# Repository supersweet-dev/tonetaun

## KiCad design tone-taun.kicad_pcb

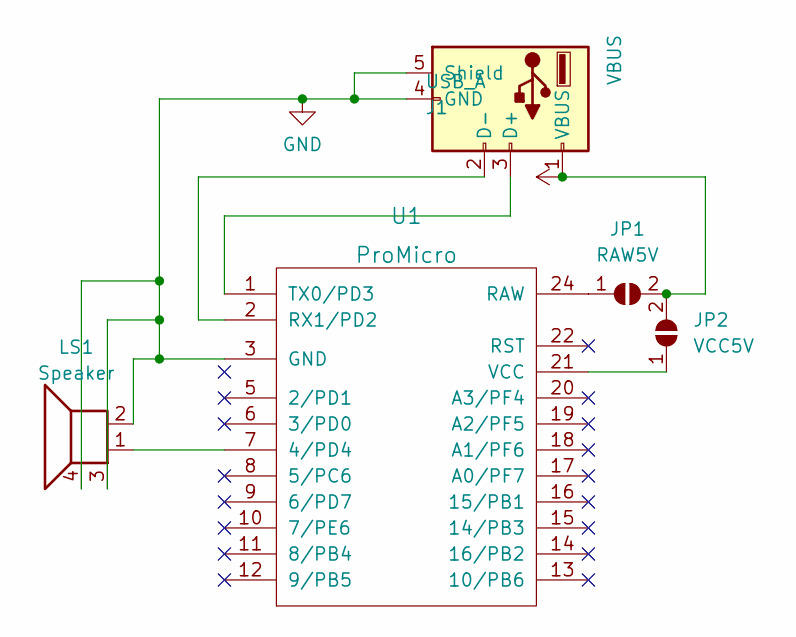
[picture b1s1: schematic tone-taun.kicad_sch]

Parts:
J1: USB_A; USB_A_TE_292303-7_Horizontal
JP1: RAW5V; SolderJumper-2_P1.3mm_Open_TrianglePad1.0x1.5mm
JP2: VCC5V; SolderJumper-2_P1.3mm_Open_TrianglePad1.0x1.5mm
LS1: Speaker; PUIAudio_SMT_0825_S_4_R
U1: ProMicro; Elite-C-castellated-24pin-holes

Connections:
GND: J1.4 (GND), J1.5 (Shield), LS1.2, LS1.3, LS1.4, U1.3 (GND), U1.4 (GND), U1.23 (GND)
unnamed: J1.2 (D-), U1.2 (RX1/PD2)
unnamed: J1.3 (D+), U1.1 (TX0/PD3)
unnamed: JP1.1 (A), U1.24 (RAW)
unnamed: JP2.1 (A), U1.21 (VCC)
unnamed: LS1.1, U1.7 (4/PD4)
VBUS: J1.1 (VBUS), JP1.2 (B), JP2.2 (B)

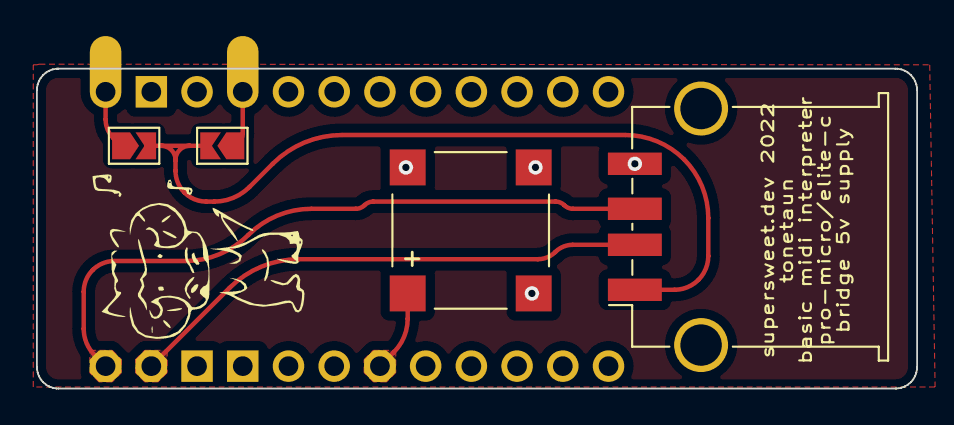
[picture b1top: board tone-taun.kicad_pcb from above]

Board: 2 copper layers, 48.9 x 17.8 mm, 5 parts (0 on the bottom side), 7 nets.

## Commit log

2022-12-10 initital commit
